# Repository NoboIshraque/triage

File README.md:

# Triage

**One app for code, circuits and 3D design, with a Run button that simulates the
whole device, or any part of it on its own.**

Engineering students write firmware in one tool, design PCBs in another and
model enclosures in a third, then copy pin numbers and re-export STEP files
between them. Nothing simulates the whole thing.

Triage is a **standalone desktop app built from VS Code's source**. It puts a
project's firmware, schematic and PCB (KiCad's engine), 3D enclosure and
mechanism (FreeCAD's engine, Blender-style UX) and renders (Blender) into one
linked project and **one window**. KiCad, FreeCAD and Blender run hidden behind
Triage's own tabs, so you never switch programs. **Run** executes the firmware on
an emulated microcontroller, drives the simulated circuit, and moves motors and
reads sensors in a 3D physics world, with automated pass/fail tests. You can also
simulate just the circuit, just the code or just the mechanism. Boards: **ESP32,
Arduino and Raspberry Pi**. Everything runs locally on a laptop, **Windows first**.

> **Status: P0 Foundations done.** Triage builds from VS Code's source on Windows
> and Linux, with its own sidebar, an Engineering layout, a native engine behind a
> broker, `triage.toml` projects and a Windows installer. Next: P1 (KiCad's engine
> inside Triage). See [docs/STATUS.md](docs/STATUS.md). The team is two: the owner
> and Claude.

## Documents

| | |
|---|---|
| [docs/STATUS.md](docs/STATUS.md) | Where we are, the next work package, confirmed decisions, defaults |
| [docs/PLAN.md](docs/PLAN.md) | Architecture: VS Code fork, hidden engines, project model, simulation kernel and scopes, decisions, risks |
| [docs/ROADMAP.md](docs/ROADMAP.md) | Phases P0–P8 as work packages with acceptance checks; milestones M1–M5 |
| [docs/GUIDELINES.md](docs/GUIDELINES.md) | How the owner and Claude build it: session routine, definition of done, forks, testing, Windows rules |
| [docs/DEVIATIONS.md](docs/DEVIATIONS.md) | Where the build differs from the plan, and why |
| [docs/adr/](docs/adr/0001-standalone-app-on-vscode-codebase.md) | Decisions: 0001 standalone app on VS Code's codebase, 0002 hidden engines, 0003 boards and Windows |
| [docs/research/](docs/research/README.md) | Full REA breakdowns of VS Code, KiCad, FreeCAD, Blender and the simulators |
| [CLAUDE.md](CLAUDE.md) | Instructions for every Claude session |

## Build from source

The setup scripts install or check everything (Node at the version in `.nvmrc`,
pnpm, Rust, CMake, Ninja, a C++ compiler; MSVC on Windows). CI builds from a
fresh machine with them:

```sh
scripts/dev/setup.sh            # Linux (Debian/Ubuntu); --check only reports, --app adds the VS Code fork's libraries
scripts\dev\setup.ps1 -DevShell  # Windows; -Check only reports, -App adds Spectre-mitigated libraries
```

Then:

```sh
pnpm install
pnpm check                      # TypeScript: build, typecheck, lint, test (Turborepo)
cargo test --workspace          # Rust
cmake --workflow --preset dev   # Triage's own native C++ (configure, build, test)
pnpm format:check               # Prettier; `pnpm format:native:check` for C/C++ (clang-format 18)
```

CI runs the same checks on Windows and Linux ([.github/workflows/ci.yml](.github/workflows/ci.yml)).

| Folder | What |
|---|---|
| `app/` | the VS Code fork (P0-2) |
| `engines/` | native engine processes: KiCad, FreeCAD, Espressif QEMU forks, render scripts, hello engine |
| `crates/` | Rust: project model, simulation kernel, solvers |
| `sim/` | Node helpers for emulators, adapters, Pi bridge, network gateway |
| `parts/` | smart part library |
| `cli/` | the `triage` command line |
| `docs/`, `scripts/` | plan and research; dev, build and research scripts |

## The core idea

```mermaid
flowchart LR
  CODE["Firmware<br/>(VS Code-based editor)"] <-->|pin map| SCH["Schematic + PCB<br/>(KiCad engine)"]
  SCH <-->|board fits enclosure| CAD["3D CAD<br/>(FreeCAD engine)"]
  CODE --> RUN(("Run"))
  SCH --> RUN
  CAD --> RUN
  RUN --> SIM["Co-simulation, whole device or any part<br/>board emulator + circuit + MuJoCo"]
  SIM --> TEST["3D playback, instruments,<br/>pass/fail tests"]
```

## How the plan was made

The real shipped builds of every tool were taken apart with **REA (Reverse
Engineer Anything)** in **unbounded mode**: no time limits and no fixed size
caps. That mode was added to the owner's fork (`NoboIshraque/rea`). The skill is
vendored in `.claude/skills/rea-full-breakdown/`, and
`scripts/research/teardown.sh` reproduces the research.

A sibling repository, `NoboIshraque/triad-extension`, keeps the earlier
alternative plan of shipping it as VS Code extensions (under the old working
name, Triad).

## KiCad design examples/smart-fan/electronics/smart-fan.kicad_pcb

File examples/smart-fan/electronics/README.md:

# Smart Fan electronics (KiCad 10)

An Arduino Uno shield (PLAN §3 step 2): an NTC thermistor divider on A0
(`TEMP_SENSE`), a logic-level MOSFET with a flyback diode driving a 12 V fan from
D9 (`FAN_PWM`), an SSD1306 OLED header on I²C (`I2C_SDA`, `I2C_SCL`), a button on
D2 (`BUTTON`) and a 12 V barrel jack.

- `smart-fan.kicad_sch`, `smart-fan.kicad_pcb`, `smart-fan.kicad_pro`: a normal
  KiCad project; it opens in stock KiCad 10. ERC and DRC report no errors; the
  board is placed but not routed yet (simple tracks arrive in P3).
- `libraries/smart_fan.*`: the symbols and footprints it uses, copied from KiCad
  10.0.8's official libraries, so the project needs no libraries installed.
- The firmware's pin constants (`../firmware/generated/board_pins.h`) are
  generated from this schematic by Triage.

`scripts/examples/smart-fan-kicad.mjs` generated these files (KiCad's own
`kicad-cli` wrote the final versions); edit them in Triage or KiCad from now on.

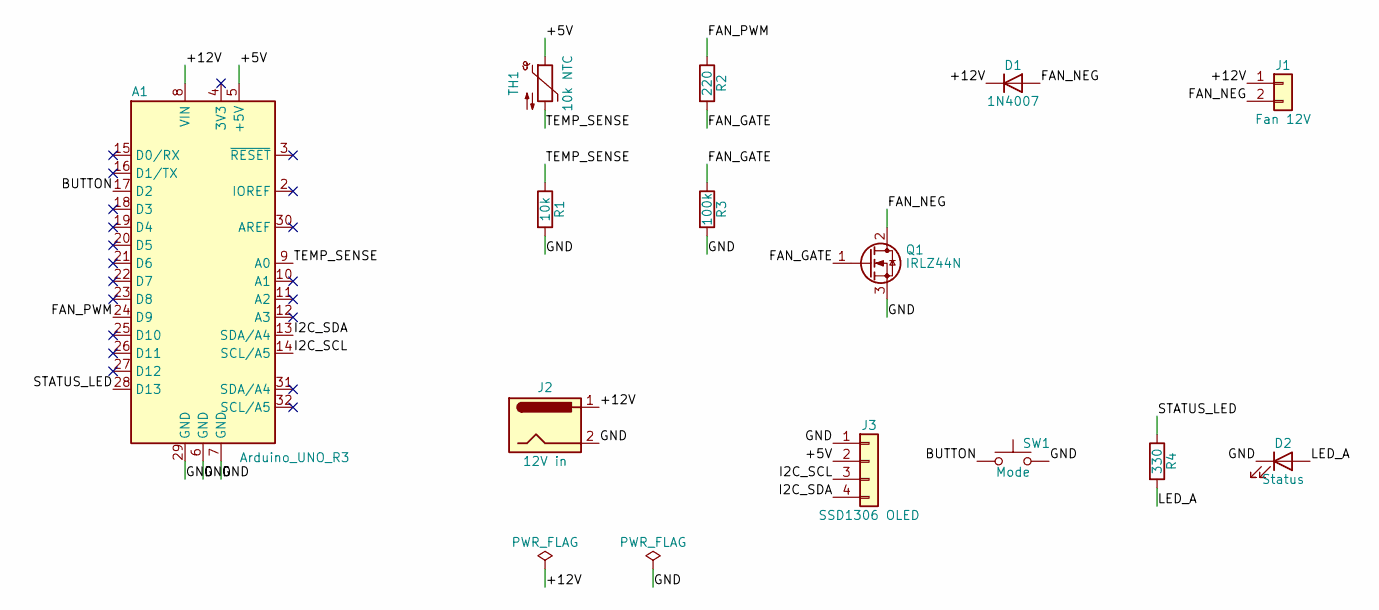
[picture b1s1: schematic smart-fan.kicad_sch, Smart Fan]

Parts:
A1: Arduino_UNO_R3
D1: 1N4007; D_DO-41_SOD81_P10.16mm_Horizontal
D2: Status; LED_D3.0mm
J1: Fan 12V; PinHeader_1x02_P2.54mm_Vertical
J2: 12V in; BarrelJack_Horizontal
J3: SSD1306 OLED; PinHeader_1x04_P2.54mm_Vertical
Q1: IRLZ44N; TO-220-3_Vertical
R1: 10k; R_Axial_DIN0207_L6.3mm_D2.5mm_P10.16mm_Horizontal
R2: 220; R_Axial_DIN0207_L6.3mm_D2.5mm_P10.16mm_Horizontal
R3: 100k; R_Axial_DIN0207_L6.3mm_D2.5mm_P10.16mm_Horizontal
R4: 330; R_Axial_DIN0207_L6.3mm_D2.5mm_P10.16mm_Horizontal
SW1: Mode; SW_PUSH_6mm
TH1: 10k NTC; R_Axial_DIN0204_L3.6mm_D1.6mm_P7.62mm_Horizontal

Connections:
/+5V: A1.5 (+5V), J3.2, TH1.1
/+12V: A1.8 (VIN), D1.1 (K), J1.1, J2.1
/BUTTON: A1.17 (D2), SW1.1
/FAN_GATE: Q1.1 (G), R2.2, R3.1
/FAN_NEG: D1.2 (A), J1.2, Q1.2 (D)
/FAN_PWM: A1.24 (D9), R2.1
/GND: A1.6 (GND), A1.7 (GND), A1.29 (GND), D2.1 (K), J2.2, J3.1, Q1.3 (S), R1.2, R3.2, SW1.2
/I2C_SCL: A1.14 (SCL/A5), J3.3
/I2C_SDA: A1.13 (SDA/A4), J3.4
/LED_A: D2.2 (A), R4.2
/STATUS_LED: A1.28 (D13), R4.1
/TEMP_SENSE: A1.9 (A0), R1.1, TH1.2

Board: 2 copper layers, 16 parts (0 on the bottom side), 12 nets, no tracks yet.

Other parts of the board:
H1, H2, H3: MountingHole_3.2mm_M3

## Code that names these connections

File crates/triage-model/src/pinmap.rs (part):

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pub struct PinAssignment {
    /// The board pin.
    pub pin: BoardPin,
    /// The net (`/FAN_PWM`); empty when nothing connects to the pin.
    pub net: String,
    /// The firmware constant for the net (`FAN_PWM`), when the net has a name.
    pub constant: Option<String>,
    /// How many other component pins share the net.
    pub others: usize,
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                lib_id: "smart_fan:Arduino_UNO_R3".into(),
                footprint: "smart_fan:Arduino_UNO_R3".into(),
                pins: vec![
                    pin("9", "A0", "/TEMP_SENSE"),
                    pin("24", "D9", "/FAN_PWM"),
                    pin("17", "D2", "/BUTTON"),
                    pin("13", "SDA/A4", "/I2C_SDA"),
                    pin("31", "SDA/A4", "/I2C_SDA"),
                    pin("25", "D10", ""),
                    pin("5", "+5V", "/+5V"),
                    pin("6", "GND", "/GND"),
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            NetComponent {
                reference: "R1".into(),
                lib_id: "smart_fan:R".into(),
                pins: vec![pin("1", "~", "/TEMP_SENSE"), pin("2", "~", "/GND")],
                ..NetComponent::default()
            },
            NetComponent {
                reference: "R2".into(),
                lib_id: "smart_fan:R".into(),
                pins: vec![pin("1", "~", "/FAN_PWM"), pin("2", "~", "Net-(Q1-G)")],
                ..NetComponent::default()
            },
            NetComponent {
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                reference: "J3".into(),
                lib_id: "smart_fan:Conn_01x04".into(),
                pins: vec![
                    pin("4", "Pin_4", "/I2C_SDA"),
                    pin("5", "Pin_5", "Net-(A1-D4)"),
                ],
                ..NetComponent::default()
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        assert_eq!(map.reference, "A1");
        let fan = map.by_number(9).expect("D9");
        assert_eq!(fan.net, "/FAN_PWM");
        assert_eq!(fan.constant.as_deref(), Some("FAN_PWM"));
        assert_eq!(fan.others, 1);
        // SDA/A4 appears twice on the Uno symbol: one net.
        assert_eq!(map.by_number(18).expect("A4").net, "/I2C_SDA");
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            .expect("pin map")
            .header("smart-fan.kicad_sch");
        assert!(
            header.contains("constexpr uint8_t FAN_PWM    =  9; // D9, PWM, net /FAN_PWM"),
            "{header}"
        );
        assert!(
            header.contains("constexpr uint8_t TEMP_SENSE = 14; // A0, analog, net /TEMP_SENSE"),
            "{header}"
        );
        assert!(
            header.contains("constexpr uint8_t I2C_SDA    = 18; // A4, SDA, analog, net /I2C_SDA"),
            "{header}"
        );
        assert!(
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    #[test]
    fn flags_unconnected_and_misused_pins() {
        let map = pin_map("arduino-uno", &smart_fan()).expect("pin map");
        let source = "#include \"board_pins.h\"\nconst int LED = 10;\nvoid loop() {\n  analogWrite(FAN_PWM, 128);\n  analogWrite(10, 3);  // the plan's example\n  analogRead(BUTTON);\n  analogWrite( 2 , 1);\n  digitalWrite(LED, HIGH);\n  int t = analogRead(A0);\n  pinMode(42, OUTPUT);\n}\n";
        let diagnostics = check_firmware(source, &map);
        let messages: Vec<(usize, usize, &str)> = diagnostics
            .iter()
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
